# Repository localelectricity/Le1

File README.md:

# L.E.One
A universal input USB power supply which makes it easy to charge your cell phone or light your home, using any type of electrical energy source. 

The power supply is able to accept DC as well as AC electricity, which is then converted into a smooth, uniform 5V for USB powered devices.

The power supply also provides feedback on how your generation device is performing through a simple UI.

# System Overview

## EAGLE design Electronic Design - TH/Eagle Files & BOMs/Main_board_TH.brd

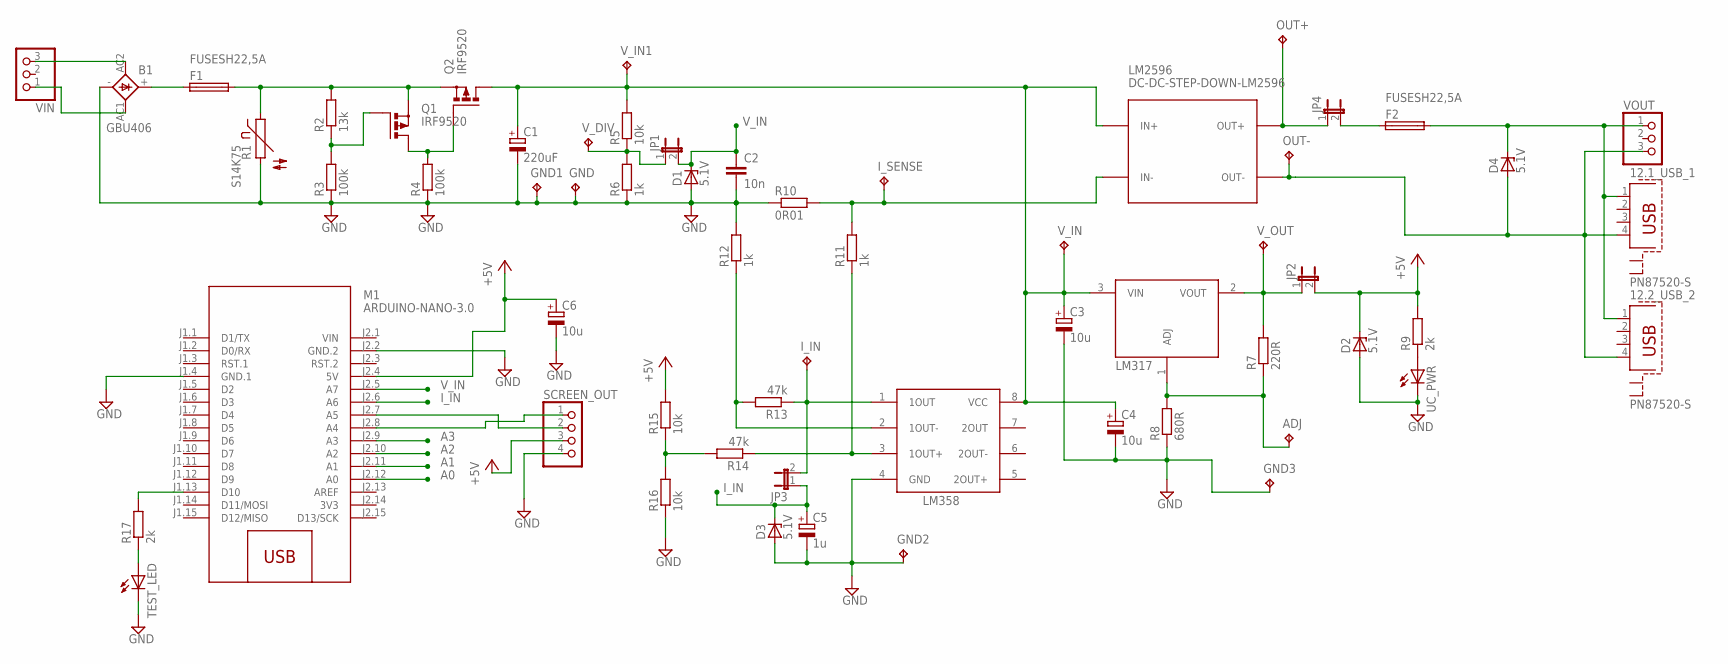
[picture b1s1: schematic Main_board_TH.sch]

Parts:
12.1_USB_1, 12.2_USB_2: PN87520-S
ADJ: TPPAD1-13; P1-13
B1: GBU406; GBU4S
C1: 220uF; E3,5-10
C2: 10n; C050-024X044
C3, C4, C6: 10u; E2,5-7
C5: 1u; E2-4
D1, D2, D3, D4: 5.1V; DO35Z10
F1, F2: FUSESH22,5A; SH22,5A
GND, GND1, GND2, GND3: TPPAD1-13; P1-13
I_IN: TPPAD1-13; P1-13
I_SENSE: TPPAD1-13; P1-13
JP1, JP2, JP3, JP4: JP1E; JP1
LM317: LM317; TO220BV
LM358: LM358; DIL08
LM2596: DC-DC-STEP-DOWN-LM2596
M1: ARDUINO-NANO-3.0
OUT+: TPPAD1-13; P1-13
OUT-: TPPAD1-13; P1-13
Q1, Q2: IRF9520; TO220BV
R1: S14K75; S14K17
R2: 13k; 0207/10
R3, R4: 100k; 0207/10
R5, R15, R16: 10k; 0207/10
R6, R11, R12: 1k; 0207/10
R7: 220R; 0207/10
R8: 680R; 0207/10
R9, R17: 2k; 0207/10
R10: 0R01; P0613/15
R13, R14: 47k; 0207/10
SCREEN_OUT: PINHD-1X4; 1X04
TEST_LED: LED3MM
UC_PWR: LED3MM
VIN: PINHD-1X3; 1X03
VOUT: PINHD-1X3; 1X03
V_DIV: TPPAD1-13; P1-13
V_IN, V_IN1: TPPAD1-13; P1-13
V_OUT: TPPAD1-13; P1-13

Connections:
3V3: M1.J2.14 (3V3)
+5V: C6.+, D2.C, JP2.2, M1.J2.4 (5V), R9.2, R15.2, SCREEN_OUT.3
A0: M1.J2.12 (A0)
A1: M1.J2.11 (A1)
A2: M1.J2.10 (A2)
A3: M1.J2.9 (A3)
GND: B1.-, C1.-, C2.2, C3.-, C4.-, C5.-, C6.-, D1.A, D2.A, D3.A, GND.TP, GND1.TP, GND2.TP, GND3.TP, LM358.4 (GND), M1.J1.4 (GND.1), M1.J2.2 (GND.2), R1.2, R3.1, R4.1, R6.1, R8.1, R10.1, R12.2, R16.1, SCREEN_OUT.4, TEST_LED.K (C), UC_PWR.K (C)
I_IN: C5.+, D3.C, JP3.1, M1.J2.6 (A6)
I_IN_PRE: I_IN.TP, JP3.2, LM358.1 (1OUT), R13.1
unnamed: B1.+, F1.1
unnamed: R9.1, UC_PWR.A
unnamed: Q1.1 (G), R2.1, R3.2
unnamed: I_SENSE.TP, LM2596.IN-, R10.2, R11.2
unnamed: LM358.3 (1OUT+), R11.1, R14.1
unnamed: LM358.2 (1OUT-), R12.1, R13.2
unnamed: B1.AC1 (AC2), VIN.1
unnamed: R14.2, R15.1, R16.2
unnamed: B1.AC2 (AC1), VIN.3
unnamed: 12.1_USB_1.4, 12.2_USB_2.4, D4.A, LM2596.OUT-, OUT-.TP, VOUT.3
unnamed: M1.J2.7 (A5), SCREEN_OUT.2
unnamed: M1.J2.8 (A4), SCREEN_OUT.1
unnamed: M1.J1.13 (D10), R17.2
unnamed: R17.1, TEST_LED.A
unnamed: JP4.1, LM2596.OUT+, OUT+.TP
unnamed: F2.1, JP4.2
unnamed: JP1.1, R5.1, R6.2, V_DIV.TP
unnamed: JP2.1, LM317.2 (VOUT), R7.2, V_OUT.TP
unnamed: ADJ.TP, LM317.1 (ADJ), R7.1, R8.2
Q2_GATE: Q1.2 (D), Q2.1 (G), R4.2
VIN: M1.J2.1 (VIN)
VIN_PROTECTED: C1.+, C3.+, C4.+, LM317.3 (VIN), LM358.8 (VCC), LM2596.IN+, Q2.2 (D), R5.2, V_IN.TP, V_IN1.TP
VIN_UNPROTECTED: F1.2, Q1.3 (S), Q2.3 (S), R1.1, R2.2
VOUT_FINAL: 12.1_USB_1.1, 12.2_USB_2.1, D4.C, F2.2, VOUT.1
V_IN: C2.1, D1.C, JP1.2, M1.J2.5 (A7)

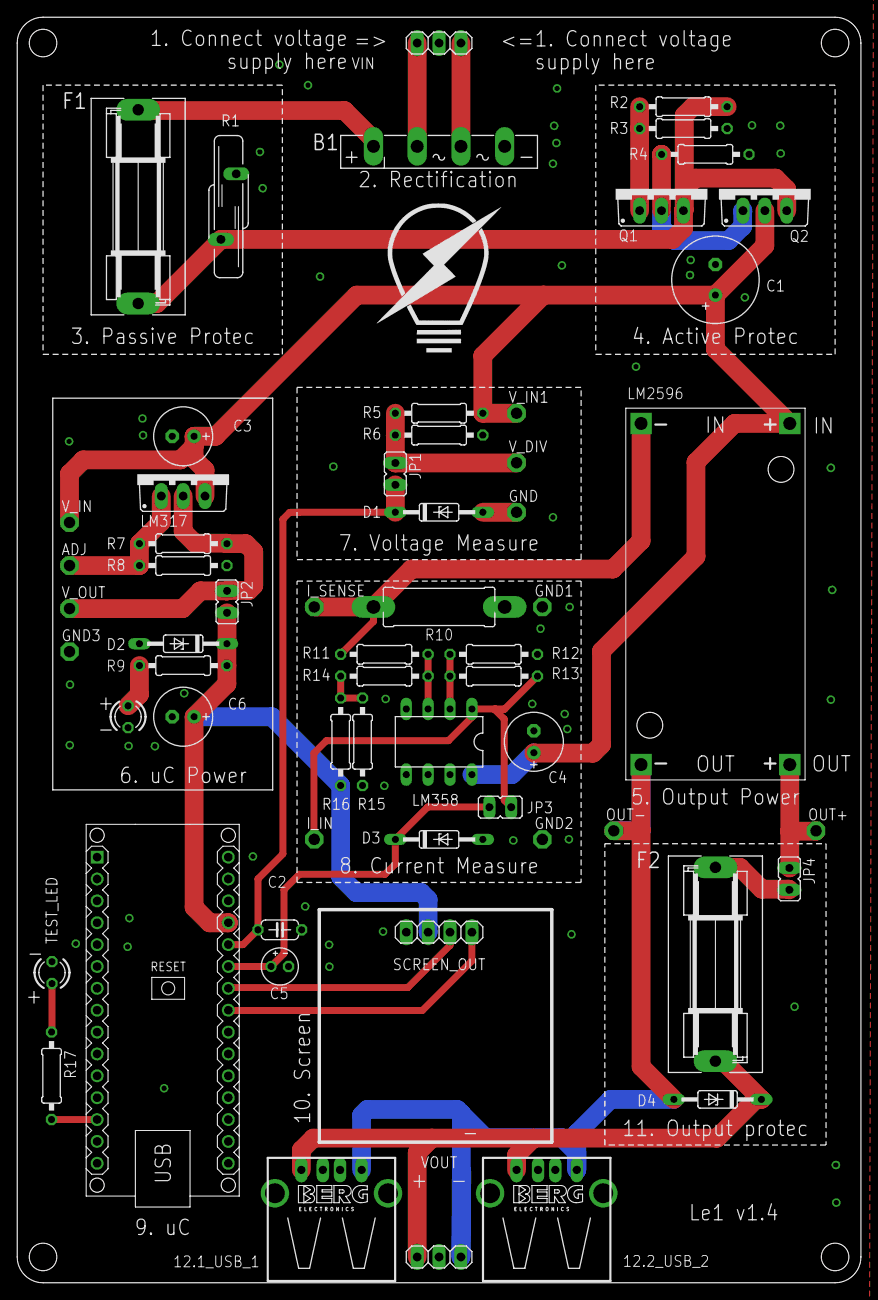
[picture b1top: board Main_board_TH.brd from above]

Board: 2 copper layers, 98.0 x 147.0 mm, 60 parts (0 on the bottom side), 28 nets.

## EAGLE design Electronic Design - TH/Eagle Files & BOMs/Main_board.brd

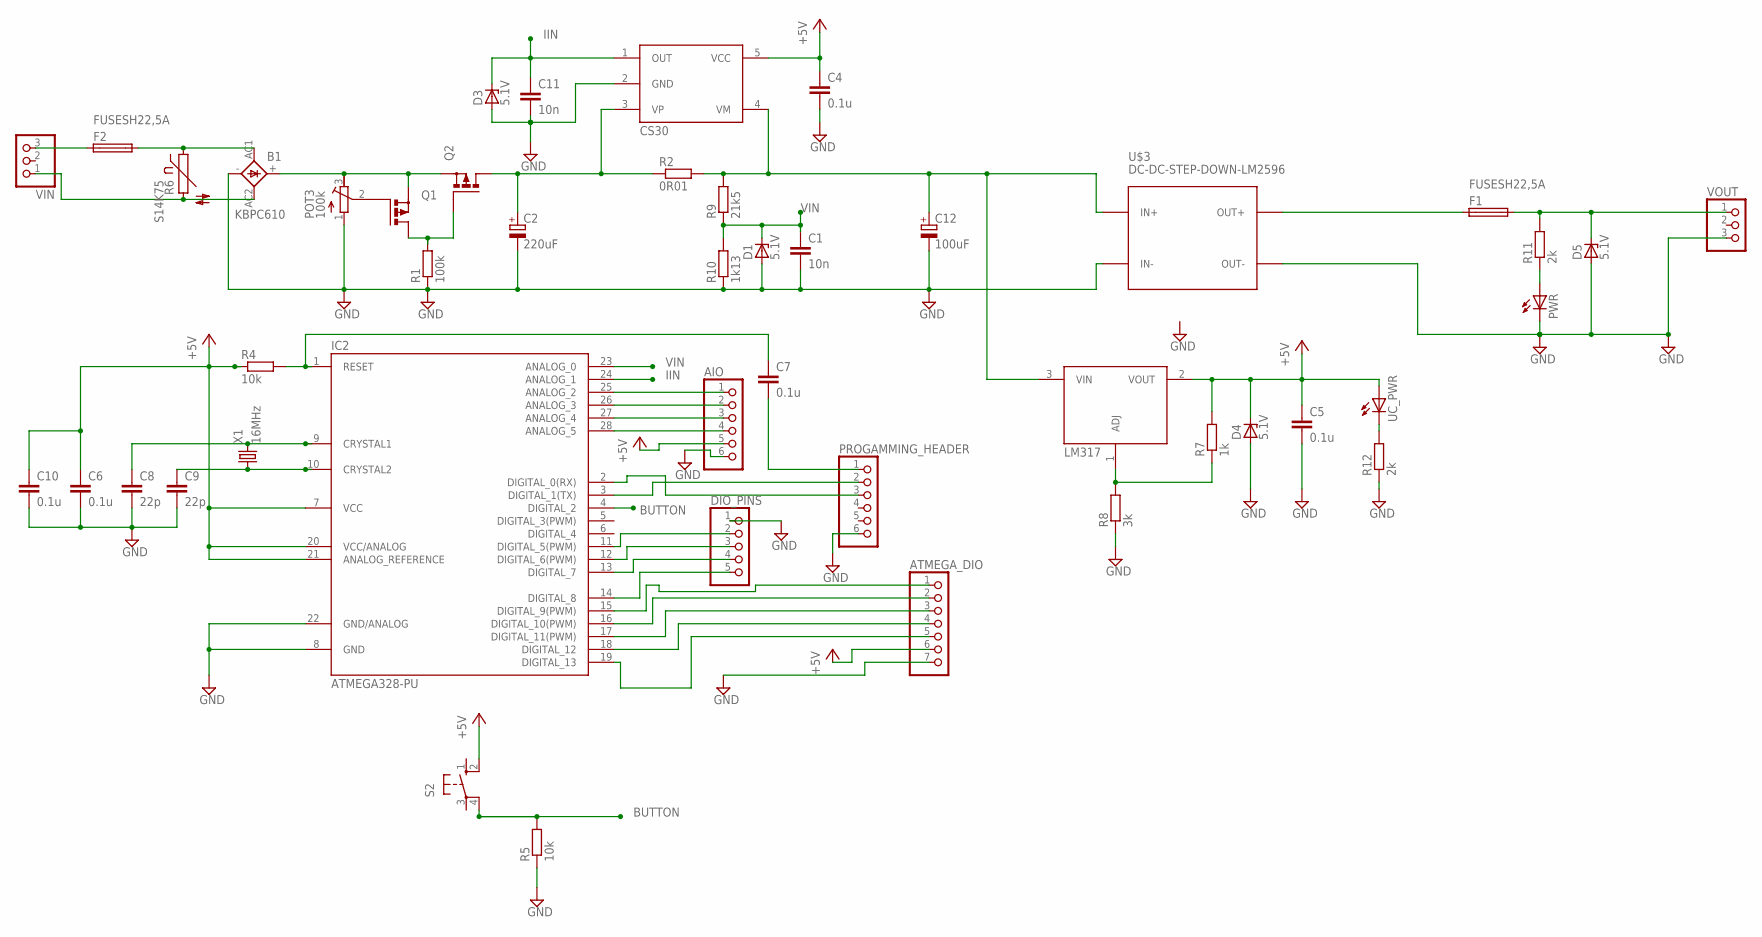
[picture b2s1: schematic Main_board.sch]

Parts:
AIO: PINHD-1X6; 1X06
ATMEGA_DIO: PINHD-1X7; 1X07
B1: KBPC610; GBPC6
C1, C11: 10n; C050-024X044
C2: 220uF; E3,5-10
C4, C5, C6, C7, C10: 0.1u; C050-024X044
C8, C9: 22p; C050-024X044
C12: 100uF; E3,5-8
D1, D3, D4, D5: 5.1V; DO35Z10
DIO_PINS: PINHD-1X5; 1X05
F1, F2: FUSESH22,5A; SH22,5A
IC2: ATMEGA328-PU; DIL28-3
POT3: 100k; RTRIM3296W
PROGAMMING_HEADER: PINHD-1X6; 1X06
PWR: LED3MM
Q1, Q2: PMOSFET_PTO220BH; TO220BH
R1: 100k; 0207/10
R2: 0R01; 0207/15
R4, R5: 10k; 0207/10
R6: S14K75; S14K17
R7: 1k; 0207/10
R8: 3k; 0207/10
R9: 21k5; 0207/10
R10: 1k13; 0207/10
R11, R12: 2k; 0207/10
S2: 10-XX; B3F-10XX
U$1: LM317; TO220BH2
U$2: CS30; SOT23-5L
U$3: DC-DC-STEP-DOWN-LM2596
UC_PWR: LED3MM
VIN: PINHD-1X3; 1X03
VOUT: PINHD-1X3; 1X03
X1: 16MHz; HC49/S

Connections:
+5V: AIO.5, ATMEGA_DIO.6, C4.1, C5.1, C6.1, C10.1, D4.C, IC2.7 (VCC), IC2.20 (VCC/ANALOG), IC2.21 (ANALOG_REFERENCE), R4.1, R7.2, S2.2 (S1), U$1.2 (VOUT), U$2.5 (VCC), UC_PWR.A
ANALOG_2: AIO.1, IC2.25 (ANALOG_2)
ANALOG_3: AIO.2, IC2.26 (ANALOG_3)
ANALOG_4: AIO.3, IC2.27 (ANALOG_4)
ANALOG_5: AIO.4, IC2.28 (ANALOG_5)
BUTTON: IC2.4 (DIGITAL_2), R5.2, S2.4 (P1)
CRYSTAL1: C8.1, IC2.9 (CRYSTAL1), X1.2
CRYSTAL2: C9.1, IC2.10 (CRYSTAL2), X1.1
D5: DIO_PINS.2, IC2.11 (DIGITAL_5(PWM))
D6: DIO_PINS.3, IC2.12 (DIGITAL_6(PWM))
D7: DIO_PINS.4, IC2.13 (DIGITAL_7)
D8: DIO_PINS.5, IC2.14 (DIGITAL_8)
D9: ATMEGA_DIO.1, IC2.15 (DIGITAL_9(PWM))
D10: ATMEGA_DIO.2, IC2.16 (DIGITAL_10(PWM))
D11: ATMEGA_DIO.3, IC2.17 (DIGITAL_11(PWM))
D12: ATMEGA_DIO.4, IC2.18 (DIGITAL_12)
D13: ATMEGA_DIO.5, IC2.19 (DIGITAL_13)
GND: AIO.6, ATMEGA_DIO.7, B1.-, C1.2, C2.-, C4.2, C5.2, C6.2, C8.2, C9.2, C10.2, C11.2, C12.-, D1.A, D3.A, D4.A, D5.A, DIO_PINS.1, IC2.8 (GND), IC2.22 (GND/ANALOG), POT3.1 (A), PROGAMMING_HEADER.6, PWR.K (C), R1.1, R5.1, R8.1, R10.1, R12.1, U$2.2 (GND), U$3.IN-, U$3.OUT-, VOUT.3
IIN: C11.1, D3.C, IC2.24 (ANALOG_1), U$2.1 (OUT)
unnamed: F2.1, VIN.3
unnamed: IC2.3 (DIGITAL_1(TX)), PROGAMMING_HEADER.2
unnamed: IC2.2 (DIGITAL_0(RX)), PROGAMMING_HEADER.3
unnamed: C7.2, PROGAMMING_HEADER.1
unnamed: PWR.A, R11.1
unnamed: R7.1, R8.2, U$1.1 (ADJ)
unnamed: R12.2, UC_PWR.K (C)
Q1_GATE: POT3.2 (S), Q1.G
Q2_GATE: Q1.D, Q2.G, R1.2
RESET: C7.1, IC2.1 (RESET), R4.2
VIN: C1.1, D1.C, IC2.23 (ANALOG_0), R9.1, R10.2
VIN_AC1: B1.AC1, F2.2, R6.1
VIN_AC2: B1.AC2, R6.2, VIN.1
VIN_CURRENT_MEASURED: C12.+, R2.2, R9.2, U$1.3 (VIN), U$2.4 (VM), U$3.IN+
VIN_PROTECTED: C2.+, Q2.D, R2.1, U$2.3 (VP)
VIN_UNPROTECTED: B1.+, POT3.3 (E), Q1.S, Q2.S
VOUT_FINAL: D5.C, F1.2, R11.2, VOUT.1
VOUT_PREFUSE: F1.1, U$3.OUT+

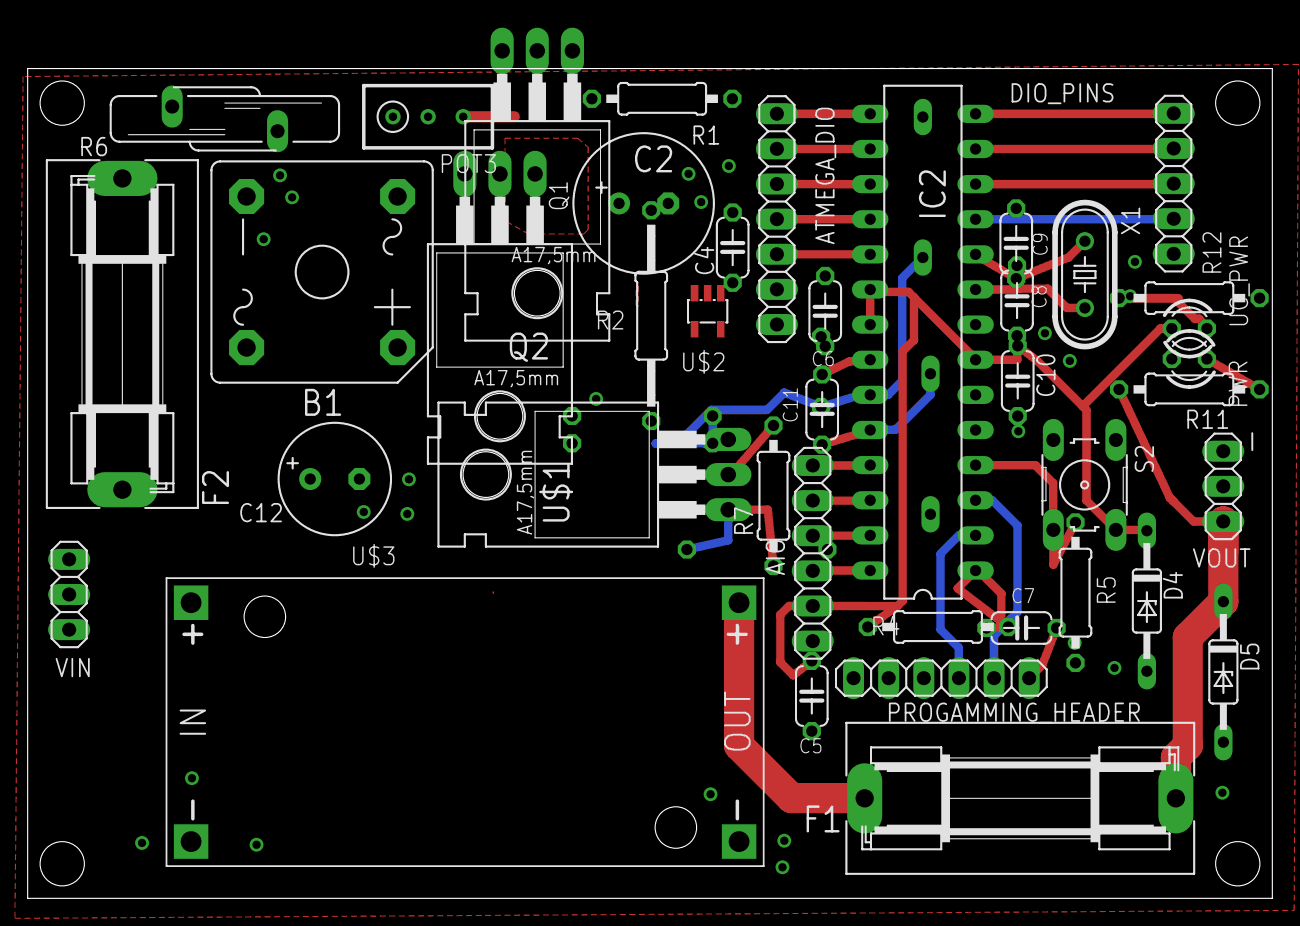
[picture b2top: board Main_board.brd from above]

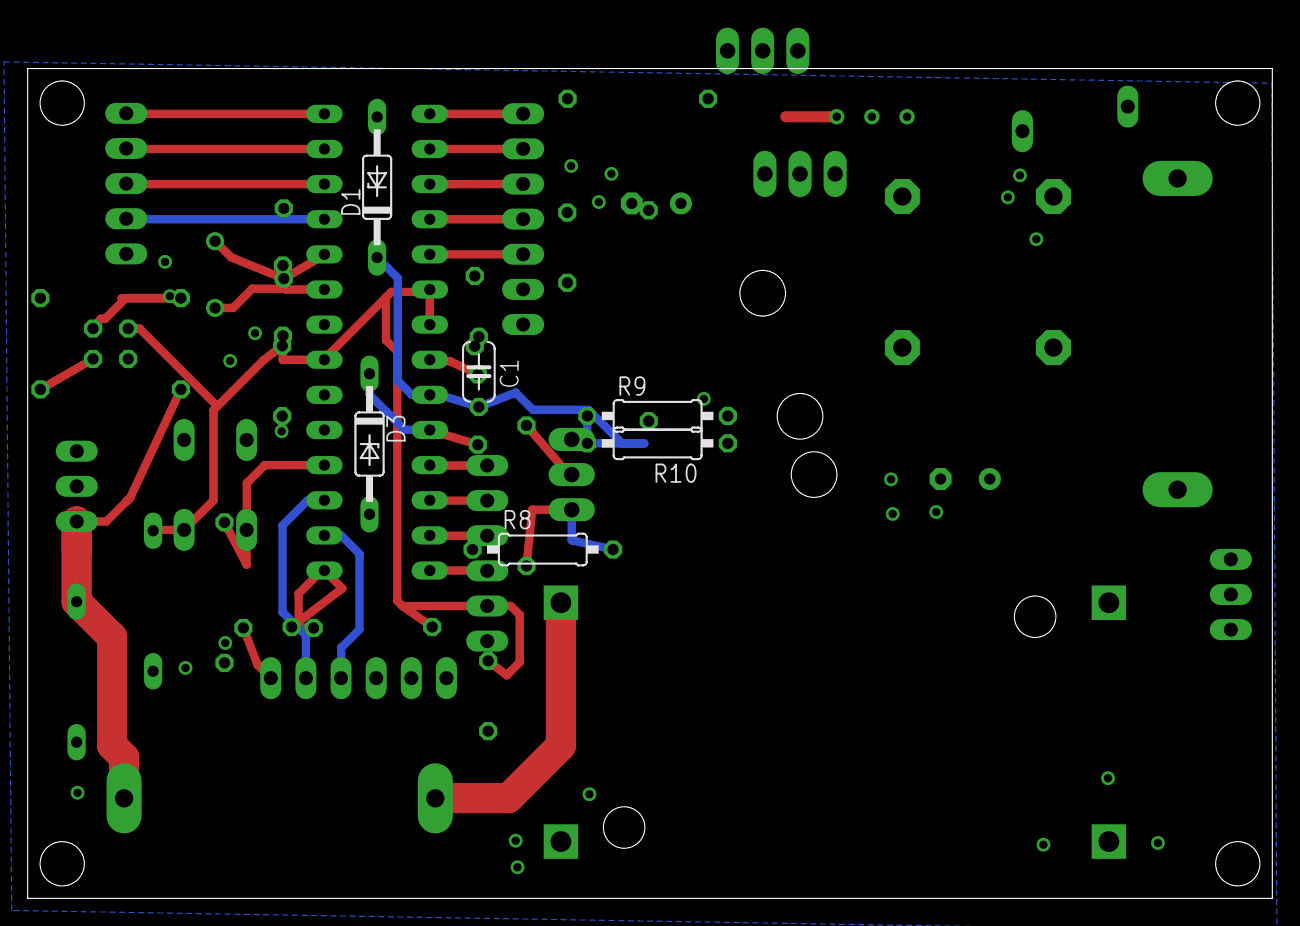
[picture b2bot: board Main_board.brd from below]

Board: 2 copper layers, 90.0 x 60.0 mm, 46 parts (6 on the bottom side), 37 nets.

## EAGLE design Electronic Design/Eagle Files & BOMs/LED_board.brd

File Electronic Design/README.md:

# Electronic Design
All electronic design files are kept here.

Contents description:

- [Eagle Files & BOMs](Eagle%20Files%20&%20BOMs): Contains all the files required to view our designs in CadSoft Eagle as well as bills of materials.

- [Gerbers](Gerbers): Contains all the files required by PCB manufacturers.

- [General Overview](General%20Overview): Contains the overview image files.

- [PDFs](PDFs): Contains PDF versions of schematics and PCB layouts of our designs.

# Block Diagramme

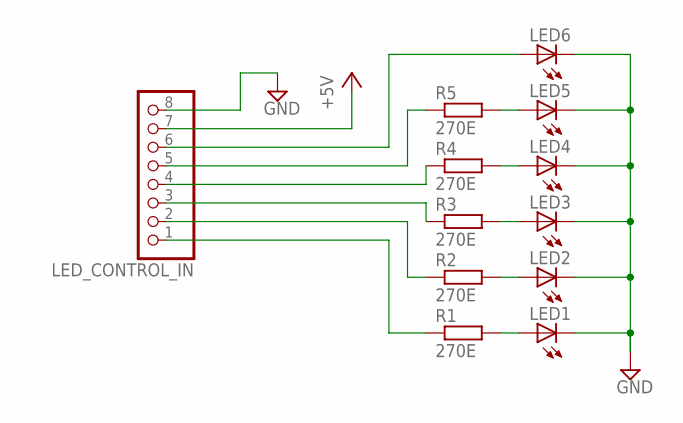
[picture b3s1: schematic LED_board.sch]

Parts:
LED1, LED2, LED3, LED4, LED5, LED6: LED5MM
LED_CONTROL_IN: PINHD-1X8; 1X08
R1, R2, R3, R4, R5: 270E; R1206

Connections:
+5V: LED_CONTROL_IN.7
GND: LED1.K (C), LED2.K (C), LED3.K (C), LED4.K (C), LED5.K (C), LED6.K (C), LED_CONTROL_IN.8
unnamed: LED_CONTROL_IN.1, R1.1
unnamed: LED_CONTROL_IN.2, R2.1
unnamed: LED_CONTROL_IN.3, R3.1
unnamed: LED_CONTROL_IN.4, R4.1
unnamed: LED6.A, LED_CONTROL_IN.6
unnamed: LED_CONTROL_IN.5, R5.1
unnamed: LED5.A, R5.2
unnamed: LED4.A, R4.2
unnamed: LED3.A, R3.2
unnamed: LED2.A, R2.2
unnamed: LED1.A, R1.2

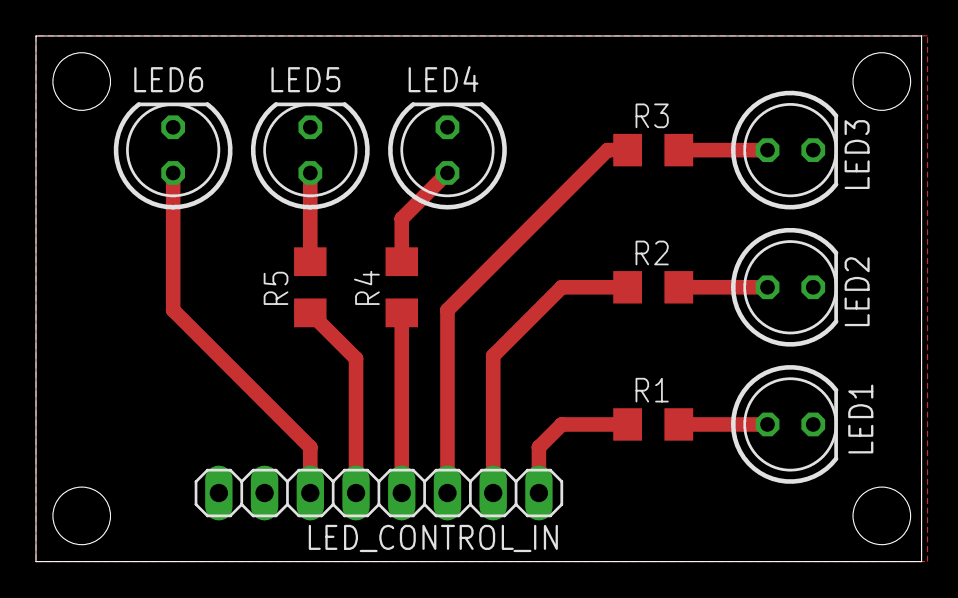
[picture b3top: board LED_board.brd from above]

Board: 2 copper layers, 49.2 x 29.2 mm, 12 parts (0 on the bottom side), 12 nets.

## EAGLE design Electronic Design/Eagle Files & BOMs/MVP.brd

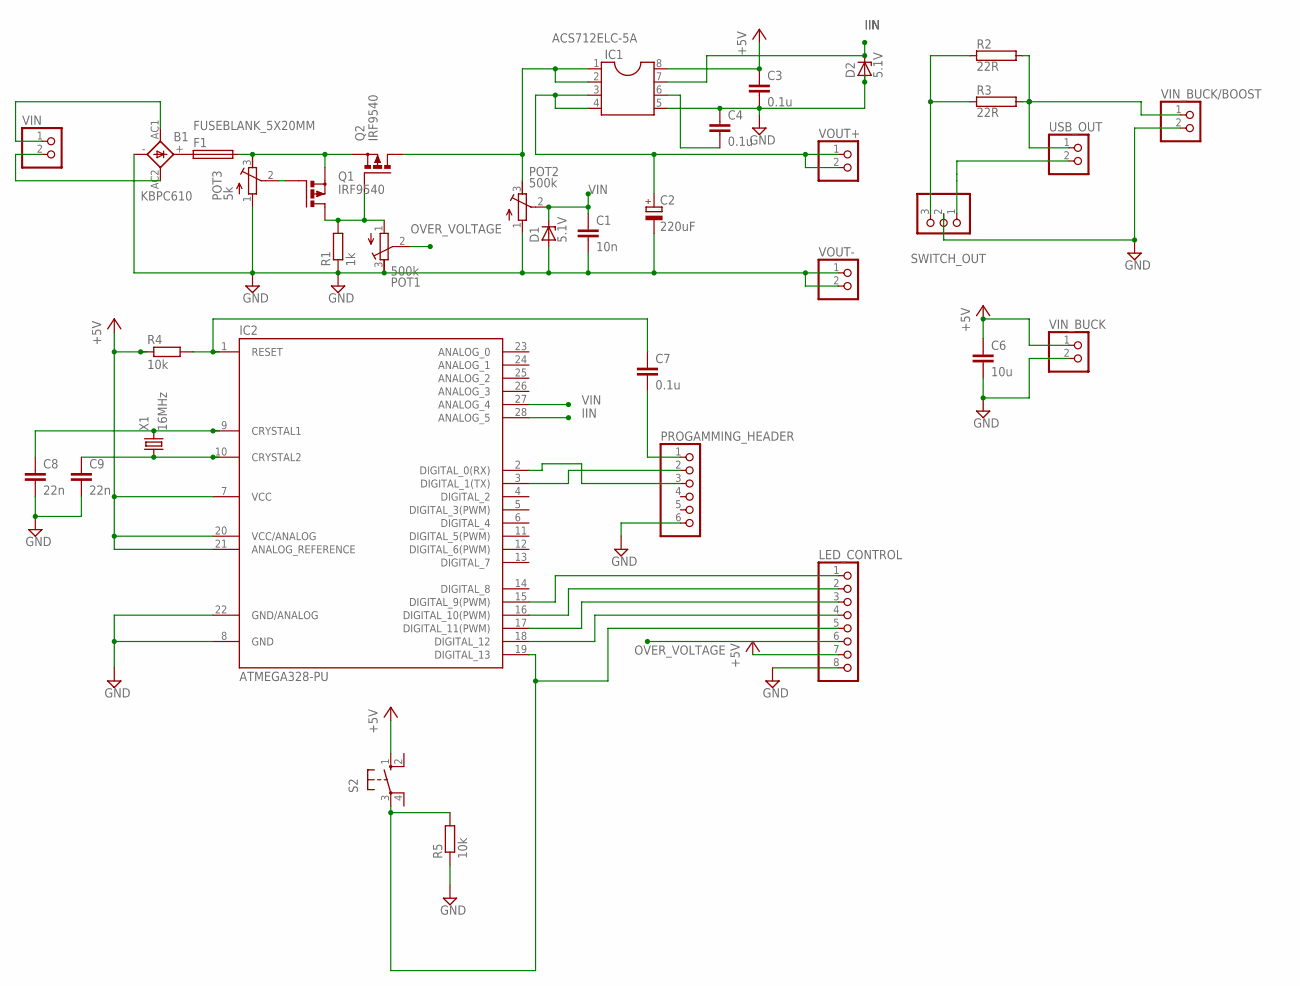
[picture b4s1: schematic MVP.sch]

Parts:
B1: KBPC610; GBPC6
C1: 10n; C1206K
C2: 220uF; E3,5-10
C3, C4, C7: 0.1u; C1206K
C6: 10u; C1206K
C8, C9: 22n; C0805K
D1, D2: 5.1V; DO35Z10
F1: FUSEBLANK_5X20MM; FUSE_HOLDER_5X20MM
IC1: ACS712ELC-5A; SOIC8
IC2: ATMEGA328-PU; DIL28-3
LED_CONTROL: PINHD-1X8; 1X08
POT1, POT2: 500k; RTRIM3296W
POT3: 5k; RTRIM3296W
PROGAMMING_HEADER: PINHD-1X6; 1X06
Q1, Q2: IRF9540; TO220BV
R1: 1k; VTA52
R2, R3: 22R; RWM8X45
R4, R5: 10k; R1206
S2: 10-XX; B3F-10XX
SWITCH_OUT: PINHD-1X3; 1X03
USB_OUT: PINHD-1X2; 1X02
VIN: PINHD-1X2; 1X02
VIN_BUCK: PINHD-1X2; 1X02
VIN_BUCK/BOOST: PINHD-1X2; 1X02
VOUT+: PINHD-1X2; 1X02
VOUT-: PINHD-1X2; 1X02
X1: 16MHz; HC49/S

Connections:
+5V: C3.1, C6.1, IC1.8, IC2.7 (VCC), IC2.20 (VCC/ANALOG), IC2.21 (ANALOG_REFERENCE), LED_CONTROL.7, R4.1, S2.1 (S), VIN_BUCK.1
GND: B1.-, C1.2, C2.-, C3.2, C4.1, C6.2, C8.2, C9.2, D1.A, D2.A, IC1.5, IC2.8 (GND), IC2.22 (GND/ANALOG), LED_CONTROL.8, POT1.3 (E), POT2.1 (A), POT3.1 (A), PROGAMMING_HEADER.6, R1.1, R5.1, SWITCH_OUT.2, VIN_BUCK.2, VIN_BUCK/BOOST.2, VOUT-.1, VOUT-.2
IIN: D2.C, IC1.7, IC2.28 (ANALOG_5)
M1S: C2.+, IC1.3, IC1.4, VOUT+.1, VOUT+.2
unnamed: B1.+, F1.1
unnamed: C4.2, IC1.6
unnamed: IC1.1, IC1.2, POT2.3 (E), Q2.D
unnamed: IC2.3 (DIGITAL_1(TX)), PROGAMMING_HEADER.2
unnamed: IC2.2 (DIGITAL_0(RX)), PROGAMMING_HEADER.3
unnamed: IC2.15 (DIGITAL_9(PWM)), LED_CONTROL.1
unnamed: POT3.2 (S), Q1.G
unnamed: IC2.19 (DIGITAL_13), LED_CONTROL.5, R5.2, S2.3
unnamed: IC2.16 (DIGITAL_10(PWM)), LED_CONTROL.2
unnamed: F1.2, POT3.3 (E), Q1.S, Q2.S
unnamed: IC2.17 (DIGITAL_11(PWM)), LED_CONTROL.3
unnamed: IC2.18 (DIGITAL_12), LED_CONTROL.4
unnamed: C7.2, PROGAMMING_HEADER.1
unnamed: C9.1, IC2.10 (CRYSTAL2), X1.1
unnamed: C8.1, IC2.9 (CRYSTAL1), X1.2
unnamed: C7.1, IC2.1 (RESET), R4.2
unnamed: B1.AC2, VIN.2
unnamed: B1.AC1, VIN.1
unnamed: R2.2, R3.2, USB_OUT.1, VIN_BUCK/BOOST.1
unnamed: R2.1, R3.1, SWITCH_OUT.3
unnamed: SWITCH_OUT.1, USB_OUT.2
unnamed: POT1.1 (A), Q1.D, Q2.G, R1.2
OVER_VOLTAGE: LED_CONTROL.6, POT1.2 (S)
VIN: C1.1, D1.C, IC2.27 (ANALOG_4), POT2.2 (S)

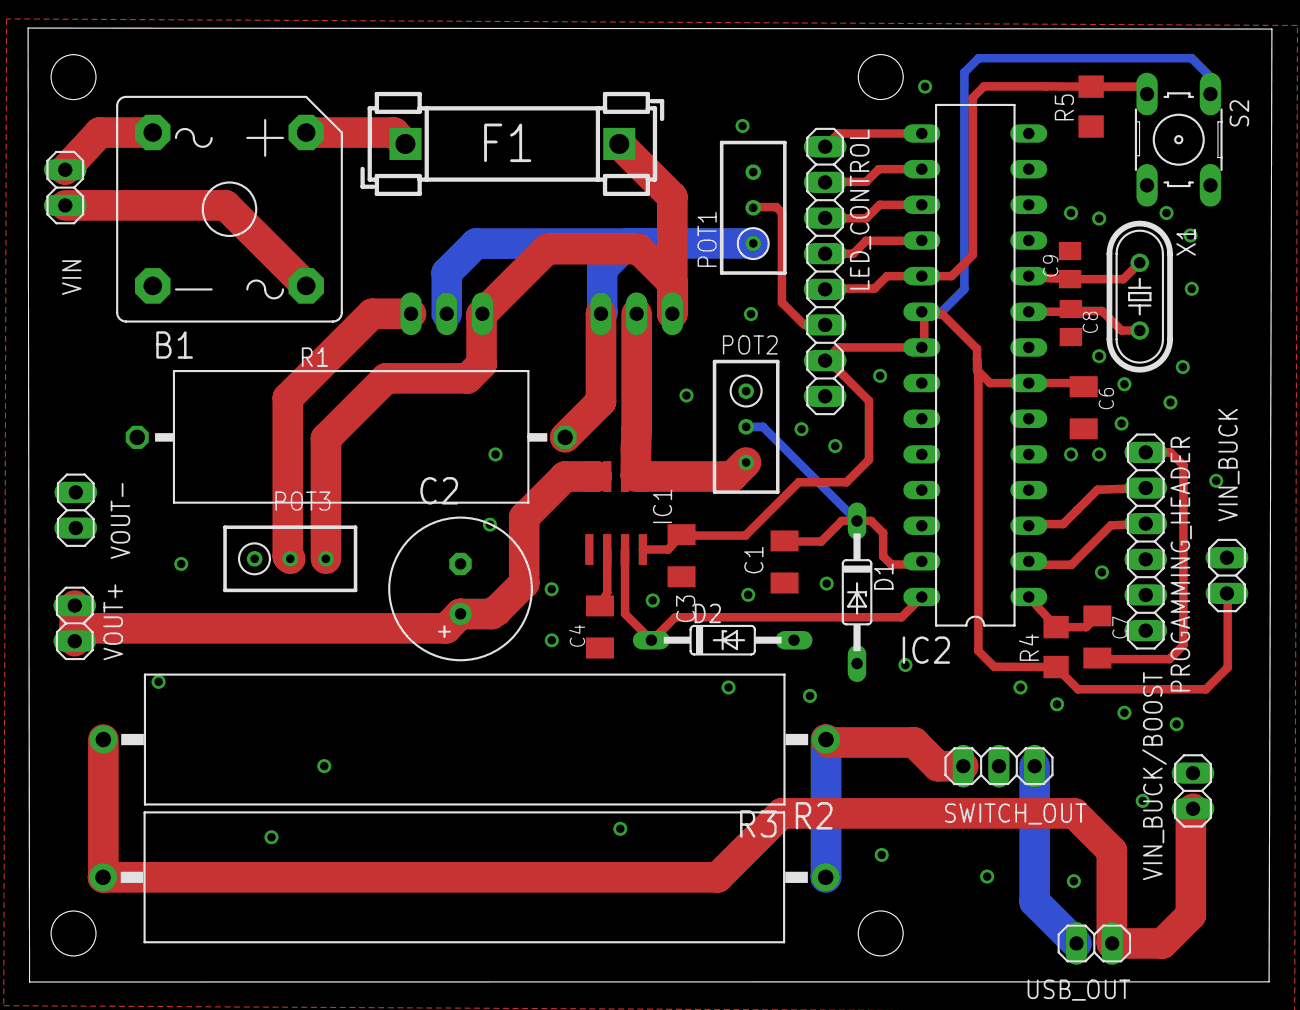
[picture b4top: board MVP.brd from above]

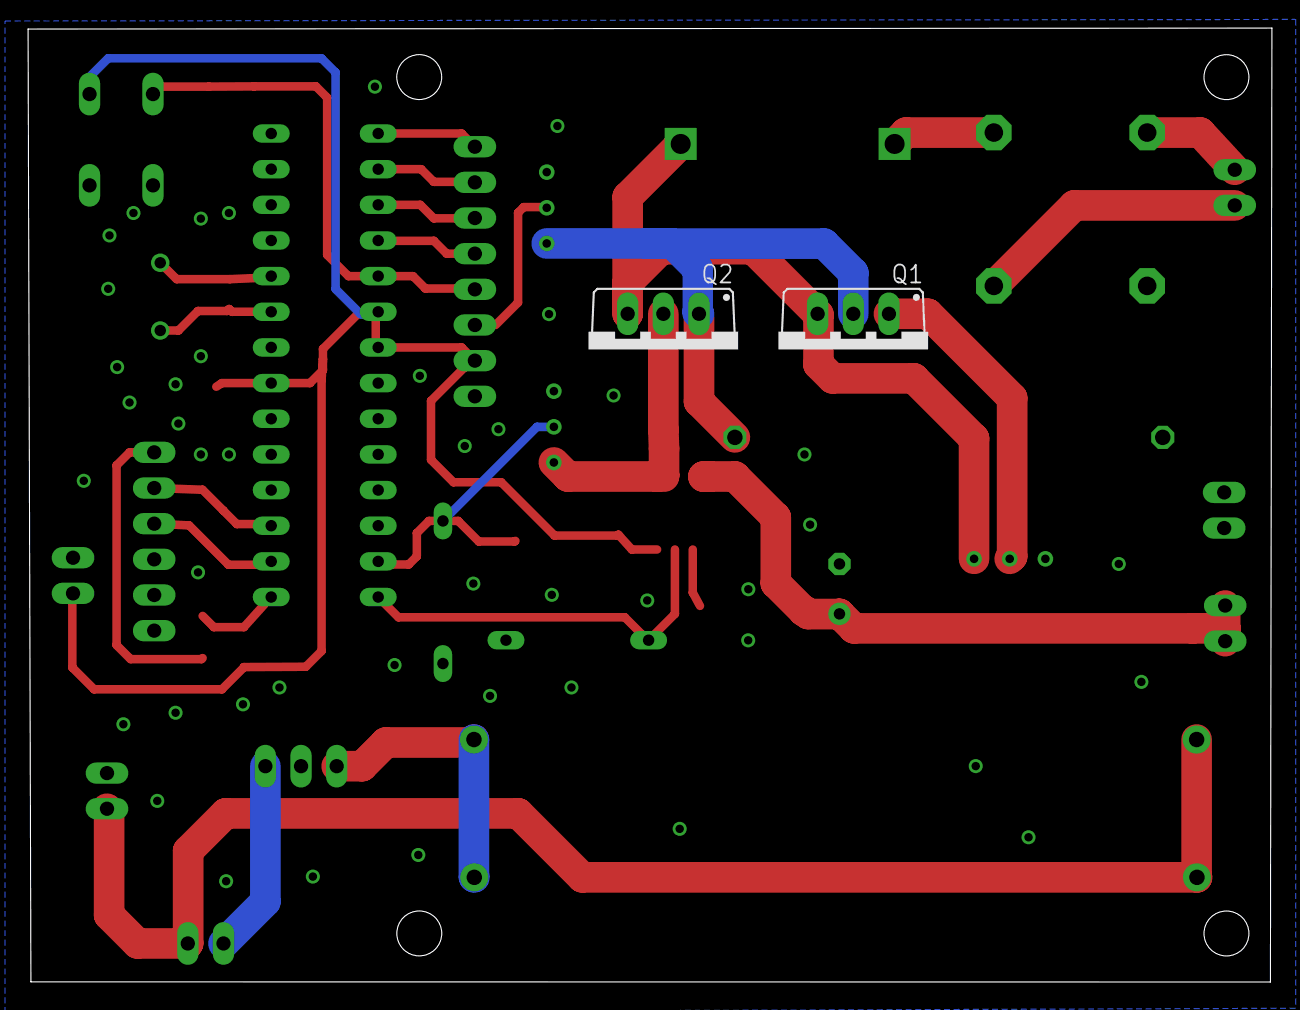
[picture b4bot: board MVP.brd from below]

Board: 2 copper layers, 88.6 x 68.0 mm, 35 parts (2 on the bottom side), 28 nets.

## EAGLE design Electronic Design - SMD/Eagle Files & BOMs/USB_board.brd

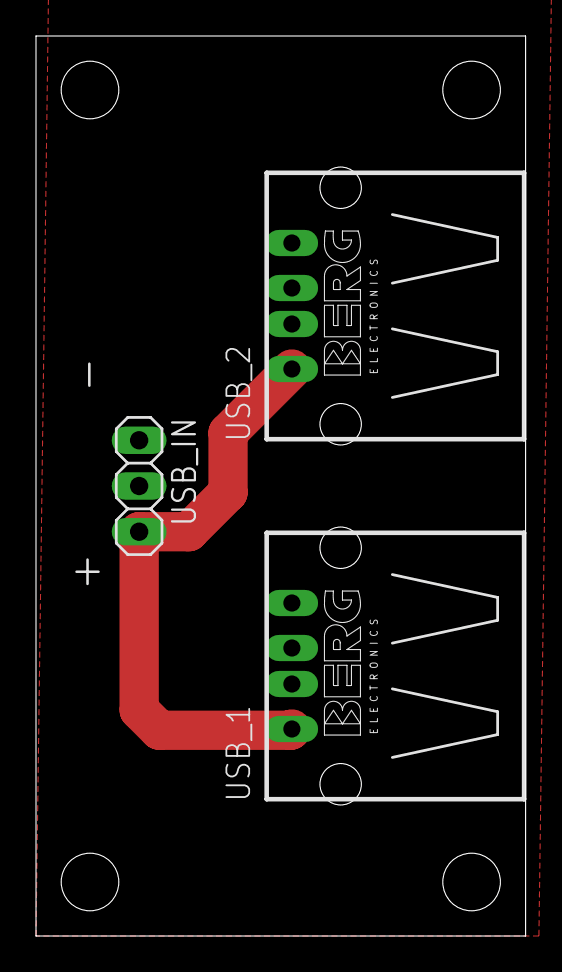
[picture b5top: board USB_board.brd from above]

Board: 2 copper layers, 27.2 x 50.0 mm, 3 parts (0 on the bottom side), 2 nets.

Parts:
USB_1, USB_2: PN87520
USB_IN: 1X03

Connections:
GND: USB_1.4, USB_2.4, USB_IN.1
unnamed: USB_1.1, USB_2.1, USB_IN.3

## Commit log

2016-08-15 Adding MVP code for arduino
2016-08-15 Adding electronic design files
2016-08-15 Changing names to allow schematic and board to be linked in eagle
2016-08-15 Removing old files
2016-08-15 Replaced .brd file with verson with some components already placed
2016-08-16 All components routed sucessfully
2016-08-16 Adjust the postion of a few components
2016-08-17 Issues seen with an offset between arduino current and voltage measurements and expected measurements. Add first pass solution at remedying this offset.
2016-08-17 Add improvements to voltage smoothing
2016-08-19 Adding changes to how power is displayed to the user by varying the intesity of LEDs. Also included are changes to serial ouput so that readings can easily be saved in CSV format
2016-08-19 adding further improvements to formatting for CSV
2016-08-19 Changing calbration offset of current measurement
2016-08-19 Adding switch and resistors for power measurement mode
2016-08-20 Code for initialisation button for current offset
2016-08-20 Adding components needed for current offset calibrations
2016-08-30 Updating changes to schematics as well as adding BOM .txt file
2016-08-30 moved components into intial places on PCB
2016-08-30 First pass at adding traces
2016-08-30 adding trace for pin16 on atmega to go to jumper
2016-08-30 Change some components connections in schematics and update board layout
    changed top and bottom layer isolation to 0.3
    completed unrouted wires
    rerouted Output to come from capacitor directly
    moved +3V3 near POT2 to allow more space forground trace to penetrate to C1 and C2
    moved decoupling caps C4 and C1 closer to IC1 and IC3, respectively
    added several ground stitching vias between top and bottom layer
2016-08-30 moved VOUT+, USB_OUT, VIN_BUCK/BOOST and VIN_BUCK closer to the edges as these will most likely be replaced with screw terminals (I couldn't find the component for these in eagle)
2016-09-07 Changed position of 5V and overvoltage on JP2
2016-09-07 Adding LED board
2016-09-08 Adding resistor values
2016-09-12 Updated circuit to reflect change from ACS711 to ACS712
2016-09-12 Changing name of IC1 to reflect change of current sensing module
2016-09-13 adding mounting holes
2016-09-13 added drill holes
2016-09-13 making board more compact and replacing pots with 3296W as these are easier to find
2016-09-13 changing resistors to 1206 size
2016-09-13 changing component names so the make sense again
2016-09-13 replacing switch on PCB with pin header as originally intended
2016-09-13 changing all caps and resistors to correct size
2016-09-13 changed code to reflect new current sensor being used
2016-09-14 flipping Q1 and Q2 back to top to save space. This is due to them never getting hot during testing so there did not seem to be a good reason for them to be on the bottom
2016-09-14 made PCB a bit smaller
2016-09-14 changed all pin headers from 7.62mm pitch to 5.08mm pitch
2016-09-14 resolved clearnace issues and sorted a connection issue between pot3 and Q1
2016-09-14 moved C2 into a more central position away from VOUT+ header
2016-09-14 MVP BOM updated and LED_board BOM created
2016-09-14 corrected names and values of components
2016-09-15 connecting two airwires that were not connected
2016-09-18 changin hole layout so that all mounting holes are he same distance from the edges
2016-09-18 connected VIN_BUCK/BOOST -ve to ground
2016-09-18 Rerouting PCB to fit the enclosure being ordered. Holes placed so that they will fit over enclosure holes
2016-09-18 Removed dimensions and cleared remaining DRC errors (mainly overlap from stray vias
2016-09-19 widening board to accomodate pin header on left hand side
2016-09-19 moved VIN+ and VIN- to allow more space between components
2016-09-20 Adding gerbers and PDF files of schematics and new file folder structure
2016-09-23 adding .zip versions of gerbers
2016-10-09 adding a readme
2016-10-09 Updating readme to include a description of the folders contained in this folder
2016-10-09 Reorganised folders to make them easier to understand
2016-10-09 updating readme
2016-10-09 updating read me
2016-10-09 changed name from device to charger
2016-10-11 updating folder structure and improving naming in MVP board
2016-10-11 removing lock files
2016-10-11 changed that name of header to LED_CONTROL_IN / OUT
2016-10-11 adding in BOMs
2016-10-11 adding overview pic
2016-10-11 adding picture to readme
2016-10-11 updating pic in readme
2016-10-11 updating readme pic
2016-10-11 adding title for pic
2016-10-11 moving pic to read me of MVP from readme of electronic design folder
2016-10-11 adding block diagramme
2016-10-12 updating block diagramme
2016-10-12 Updating block diagramme, removing 1 for buck/boost converter name
2016-10-12 updated description, changing word charger to power supply
2016-10-12 changed name of firmware folder
2016-10-12 adding readme
2016-10-12 cirrecting spelling mistake
2016-10-19 correcting spelling mistake
2016-10-19 updated links to relative links
2016-10-19 updating fonts on system overview files
2016-10-23 Updating names from MVP to L.E.One
2016-10-23 Updating names
2016-11-02 correcting cap values on atmega crystal
2016-11-02 updating pdf and BOM with new cap values
2016-11-23 added overvoltage protection, replaced fuse holder footprint, stopped irfs from overlapping with ground stitching vias, moved dummy load resistors and corrected pin header pitch
2016-11-24 Adding extra breakouts for atmega pins and USB connectivity
2016-11-24 moved vias
2016-11-24 adding final routing
2016-11-28 moving termin points for outputs
2016-11-28 adding breakout for atmega analog pins
2016-11-28 redrawing board
2016-11-28 moving terminal outputs into better postions
2016-11-28 adding header for additional DIO pins
2016-11-28 fixing minor drc errors and repostionings monting holes
2016-11-28 fixing another minor drc
2016-11-28 making dem #tracks look more #beautiful.
2016-11-28 another flicking drc error
2016-11-29 adding an untraced wire
2016-12-15 Adding OLED interface and gauge UI
2017-02-13 removing dummy load and adding in lm2596 boards to PCB
2017-02-14 Tidying up names
2017-02-14 adding feedback from Angus
2017-02-14 removing pesky files
2017-02-14 removing LED board files
2017-02-14 adding USB_board
2017-02-15 moving placement of Vin terminal
2017-03-02 reducing size of USB board
2017-03-02 adding in new AIO pin header
2017-03-02 made PCB smaller
2017-03-03 minor changes to PCB and updating gerbers
2017-03-03 minor changes to USB board and updating gerbers
2017-03-09 adding updated gerbers and moving name of arduino DIO
2017-03-16 adding in variable for voltage and current pins and setting to new pins due to PCB changes
2017-04-13 adding new current sensor and buck converter for USB power supply
2017-04-14 adding new arduino voltage reg and improved schematic symbol for CS30
2017-04-14 Adding in inductor and feedback to LM2576
2017-04-14 replacing lm2596 package with lm2576 package
2017-04-14 Minor changes (no idea what it is but it should be minor)
2017-04-15 addig smoothing caps for LM317 out and CS80 inputs
2017-04-19 adding smoothing caps and zeners to Iin
2017-04-19 adding hardwired voltage divider for Vin measurement
2017-04-21 adding new layout of PCB
2017-04-25 adding ground to AIO and general tidy up
2017-06-10 Moving fuse close to output rather than input
2017-06-11 adding 5.1v zeners and LEDs to outputs of voltage regulators
2017-06-11 Adding new overvoltage protection FETs and renaming nets
2017-06-11 Moving everything into postion and adding fuse to start of circuit
2017-06-11 moving everything into place and DRC check complete
2017-06-13 Moving buck converter and re-arranging other components as needed
2017-06-14 Tidying up ground planes and traces. Adding ground stitching vias
2017-06-14 tidying up component names on silkscreen
2017-06-20 Don't know
2017-06-25 replacing homemade buck converter with premade board
2017-06-25 rerouting overlap
2017-06-26 moving res divider for vin measurement to bottom of PCB
2017-06-26 moving input terminal closer to edge of pcb
2017-06-26 mocing component names to be in better places (not overlapping pads)
2017-08-25 final commit
2017-09-03 adding new Through hole folder
2017-09-03 replaced SMD resistors, caps and MOSFETs with TH components
2017-09-04 correcting mosfet postion
2017-09-18 renamed files to reflect two versions of L.E.One and replacing ATmega 328 with arduino nano
2017-09-18 replacing CS30 with LM358
2017-09-18 replacing divider resistors for voltage measurement
2017-09-18 Adding names of Q1 and Q2
2017-09-18 removing .zip file
2017-09-18 adding ground to arduino
2017-09-25 Moving varistor to after rectification stage
2017-09-25 Moving fuse to after recification stage
2017-09-25 removing ground connections from output of LM2596
2017-10-15 Removed: pin headers for arduino, button for arduino and LED for LM2596. Inital board layout complete. Sub modules pretty much done but overall layout still needs work
2017-10-15 high level layout complete and adding in BOM
2017-10-16 completing passive protection and active protection alignment and renaming components sequentially (i.e. R1, R2, R3, ...)
2017-10-16 completing power supply alignment and voltage measurement alignment
2017-10-16 All placements finished
2017-10-16 Routing completed
2017-10-16 adding in USB outputs
2017-10-16 Minor cosmetic changes
2017-10-16 adding logo to the front of the board
2017-10-17 Redoing names of sections so that they fit and adding in versioning and a place for people to put their names
2017-10-17 minor cosmetic changes in the silkscreen layer
2017-10-17 reducing board size by 0.2mm to get it bang on 137mm
2017-10-18 redoing readme to reflect new path to overview image
2017-10-18 updating PDF and gerber files
2017-10-25 updating values of divider on Q1
2017-12-08 updating firmware and correcting screen pins
2017-12-13 adding in new LED for testing and widening board
2017-12-17 adding in test points and jumpers
2017-12-17 putting all components into the right places before rounting
2017-12-17 adding another jumper after current sensing and more routing done
2017-12-18 finishing routing
2017-12-18 adding bottom layouts - arrows done
2017-12-18 adding in names of main areas in block diagramme
2017-12-19 adding in numbers for items on block diagramme
2017-12-19 correcting top silkscreen
2017-12-19 correcting bottom silkscreen
2017-12-19 final touches
2018-01-24 adding test points for LM317
2018-01-24 moving LM317 to be centered
2018-01-24 neraming jumpers, changing hole size of r10 and monor adjustments to underside of PCB
2018-01-24 Moving r10 lable
2018-01-24 changing version number on board
2018-07-11 changing size of pads on board and redoing firmware to reflect actual current
2018-07-11 replacing C5 with 1uf polarised cap
2018-07-11 adding new gerbers and gitignorfile
2019-05-17 adding in new Le1 and some changes toTH Main baord
2019-05-17 adding in TH firmware and moving things around and updating TH firmware to work with latest adafruit libs for the screen
2019-07-26 minor changes made
2019-07-26 adding rounded corners
2019-07-26 adding new gerbers
2019-09-03 adding in measurement points for output of main voltage regulator and adding in polarity for LEDs

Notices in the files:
parts and their libraries:
diy-modules: Released under the Creative Commons Attribution 4.0 International License: http://creativecommons.org/licenses/by/4.0
